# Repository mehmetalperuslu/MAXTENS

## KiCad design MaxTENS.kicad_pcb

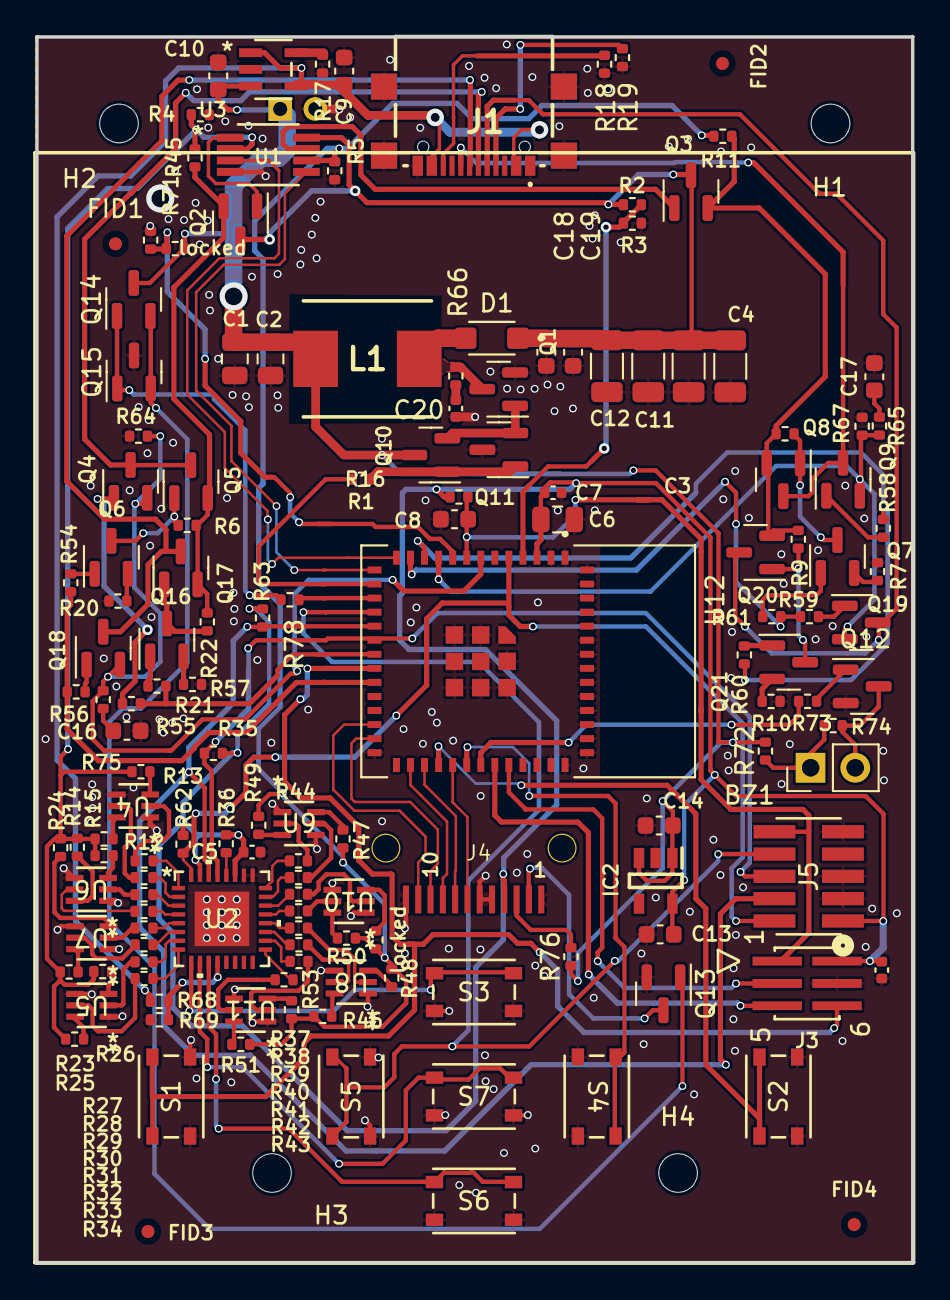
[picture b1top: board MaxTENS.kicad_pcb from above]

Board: 2 copper layers, 49.9 x 69.8 mm, 154 parts (1 on the bottom side), 128 nets.

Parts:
BZ1: Buzzer; PinHeader_1x02_P2.54mm_Vertical
C1, C2: 10uF; C_0805_2012Metric
C3, C4, C11, C12: 2.2u; C_1206_3216Metric
C5, C7, C15, C20: 0.1u; C_0402_1005Metric
C6: 22u; C_0805_2012Metric
C8, C9, C10, C13, C14, C16, C17: 1u; C_0603_1608Metric
C18: 0.1u; C_0603_1608Metric
C19: 10n; C_0603_1608Metric
D1: DSS18UTR; SODFL3618X110N
FID1, FID2, FID3, FID4: Fiducial; Fiducial_0.75mm_Mask1.5mm
H1, H2, H3, H4: MountingHole; MountingHole_2.2mm_M2
IC2: AP7366-33W5-7; SOT95P285X130-5N
J1: GSB1C41110SSHR
J3: 20021121-00006C4LF; CONN_20021121-00006C4LF_AMP
J4: Conn_01x12; FPC_TFT_LCD
J5: 20021121-00010C4LF; CONN_00010C4LF_AMP
J6: Conn_01x02_Pin; PinHeader_1x02_P2.00mm_Vertical
L1: 22uH; INDPM7366X300N
Q1: PMV37ENEAR; SOT-23
Q2, Q3, Q4, Q6, Q7, Q9, Q10, Q12, Q14, Q16, Q18, Q19, Q21: NPN; SOT-23
Q5, Q8, Q11, Q15, Q17, Q20: PNP; SOT-23
Q13: T2N7002BK,LM; SOT-23
R1, R78: 100; R_0402_1005Metric
R2: 200k; R_0402_1005Metric
R3, R13, R16, R35, R36, R49, R62, R63, R66, R68, R69: 10k; R_0402_1005Metric
R4, R5: 30k; R_0402_1005Metric
R6, R8, R9, R22, R71: 100k; R_0402_1005Metric
R7, R10, R20, R21: 1k; R_0402_1005Metric
R11, R45: 16k; R_0402_1005Metric
R12, R47: 1M; R_0402_1005Metric
R14, R50: 4.99k; R_0402_1005Metric
R15: 3.3k; R_0402_1005Metric
R17, R24, R48: 2k; R_0402_1005Metric
R18, R19: 2.2k; R_0402_1005Metric
R23, R46: 2.4k; R_0402_1005Metric
R25, R51: 1.43k; R_0402_1005Metric
R26, R53: 1.1k; R_0402_1005Metric
R27, R28, R29, R30, R31, R32, R33, R34, R37, R38, R39, R40, R41, R42, R43, R44: 510; R_0402_1005Metric
R54, R55, R56, R57, R58, R59, R60, R61: 300; R_0402_1005Metric
R64, R67: 15; R_0402_1005Metric
R65, R75: 5k; R_0402_1005Metric
R72, R73, R74: 1K; R_0402_1005Metric
R76: 10; R_0402_1005Metric
S1, S2, S3, S4, S5, S6, S7: PTS815 SJM 250 SMTR LFS; SW4_PTS815 SJM 250 SMTR LFS_CNK
U1: ADA4522-2ARMZ-R7
U2: PCAL6524HEAZ; HUQFN32_PCAL6524_NXP
U3: MCP73812T-420I/OT; SOT-23-5_MC_MCH
U4, U5, U6, U7, U8, U9, U10, U11: 2N7002KDW_R1_00001; SOT-363-6_2P2X1P35_ONS
U12: ESP32-MINI-1-N4; XCVR_ESP32-MINI-1-N4
locked: 3.3k; R_0402_1005Metric
locked#2: 33k; R_0402_1005Metric

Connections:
+3.3V: C5.2, C6.1, C7.1, C13.1, C15.2, IC2.5 (OUT), J3.1, J4.4, J5.1, R16.1, R35.1, R36.1, R62.1, R63.1, U2.27 (VDD(P)), U2.31 (VDD(I2C-BUS)), U12.3 (3V3)
+5V: C9.1, J1.A4 (VBUS_1), J1.A9 (VBUS_2), R68.2, U3.1 (CE), U3.4 (VDD)
+BATT: C1.1, C2.1, C10.1, C14.1, IC2.1 (IN), IC2.3 (EN), J6.1, L1.1, Q10.3 (C), Q14.3 (C), R72.2, R76.1, U3.3 (VBAT), locked#2.2
+OUT_1: Q2.2 (E), Q5.2 (E), Q17.2 (E), R6.2, R22.2, R45.1
+OUT_2: Q3.2 (E), Q8.2 (E), Q20.2 (E), R8.2, R9.2, R11.2
/BatteryCharger/BAT_CHG: R68.1, R69.2, U2.12 (P1_3)
/BatteryCharger/BAT_LEVEL: R71.2, U12.9 (I34), locked#2.1
/BatteryCharger/CH1_N: J1.A7 (DN1), Q17.3 (C), Q18.3 (C)
/BatteryCharger/CH1_P: J1.A6 (DP1), Q4.3 (C), Q5.3 (C)
/BatteryCharger/CH2_N: J1.B7 (DN2), Q19.3 (C), Q20.3 (C)
/BatteryCharger/CH2_P: J1.B6 (DP2), Q8.3 (C), Q9.3 (C)
/BoostConverter/VFB: R2.2, R3.1, U12.4 (I36)
/BoostConverter/VSW: R1.1, U12.15 (IO27)
/ElectrodeChannels/CH1_1: R55.2, R57.2, U12.20 (IO2)
/ElectrodeChannels/CH1_2: R54.1, R56.1, U12.22 (IO4)
/ElectrodeChannels/CH2_1: R58.2, R60.2, U12.11 (IO32)
/ElectrodeChannels/CH2_2: R59.1, R61.1, U12.12 (IO33)
/ElectrodeChannels/EL1_DET: Q4.2 (E), Q18.2 (E), R64.1, R75.2, U12.7 (I39)
/ElectrodeChannels/EL2_DET: Q9.2 (E), Q19.2 (E), R65.2, R67.1, U12.10 (I35)
/LCD/CLK: J4.9, U12.29 (IO5)
/LCD/CS: J4.8, U12.30 (IO18)
/LCD/DC: J4.7, U12.32 (IO19)
/LCD/DIN: J4.10, U12.26 (IO10)
/LCD/LCD_A: J4.3, R76.2
/LCD/LCD_BL: R78.1, U12.16 (IO14)
/LCD/LCD_K: J4.2, Q13.3 (D)
/LCD/RST: J4.11, U12.25 (IO9)
/MCU/BUZZER_MCU: R73.2, U12.34 (IO21)
/MCU/BUZZER_N: BZ1.2 (+), Q12.3 (C), R74.1
/MCU/BUZZER_P: BZ1.1 (-), R72.1, R74.2
/MCU/CH1_BTN: J3.5, S1.1, S1.2, U12.21 (IO0)
/MCU/CH2_BTN: S2.1, S2.2, U12.31 (IO23)
/MCU/EN: C8.2, J3.2, J5.10, R16.2, U12.8 (EN)
/MCU/IN1: U1.5 (INB+), U12.14 (IO26)
/MCU/IN2: U1.3 (INA+), U12.13 (IO25)
/MCU/INT_IO_EXP: J5.2, R62.2, U2.32 (*INT), U12.5 (I37)
/MCU/LEFT_BTN: S4.1, S4.2, U12.33 (IO22)
/MCU/MOSI: J5.4, R63.2, U2.30 (SDA), U12.18 (IO13)
/MCU/RIGHT_BTN: J5.8, S5.1, S5.2, U12.17 (IO12)
/MCU/RXD: J3.6, U12.35 (RXD0)
/MCU/SCK: J5.6, R35.2, U2.29 (SCL), U12.19 (IO15)
/MCU/TXD: J3.4, U12.36 (TXD0)
/Opamp/MODE_BTN: S6.1, S6.2, U2.11 (P1_2)
/Opamp/OK_BTN: S7.1, S7.2, U2.10 (P1_1)
/Opamp/OUTA: Q2.1 (B), U1.1 (OUTA)
/Opamp/OUTB: Q3.1 (B), U1.7 (OUTB)
/Opamp/P0W: R4.1, R12.1, R13.1, R14.1, R15.1, R23.1, R24.1, R25.1, R26.1, R45.2, U1.2 (INA-)
/Opamp/P1W: R5.1, R11.1, R46.1, R47.1, R48.1, R49.1, R50.1, R51.1, R53.1, U1.6 (INB-), locked.1
/Opamp/P05V: R27.1, U4.2 (G)
/Opamp/P010: R28.1, U4.5 (G)
/Opamp/P015: R29.1, U6.2 (G)
/Opamp/P15V: R37.1, U9.2 (G)
/Opamp/P020: R30.1, U6.5 (G)
/Opamp/P025: R31.1, U7.2 (G)
/Opamp/P030: R32.1, U7.5 (G)
/Opamp/P040: R33.1, U5.2 (G)
/Opamp/P050: R34.1, U5.5 (G)
/Opamp/P110: R38.1, U9.5 (G)
/Opamp/P115: R39.1, U10.2 (G)
/Opamp/P120: R40.1, U10.5 (G)
/Opamp/P125: R41.1, U8.2 (G)
/Opamp/P130: R42.1, U8.5 (G)
/Opamp/P140: R43.1, U11.2 (G)
/Opamp/P150: R44.1, U11.5 (G)
/Opamp/TIMER_BTN: S3.1, S3.2, U2.9 (P1_0)
GND: C1.2, C2.2, C3.2, C4.2, C5.1, C6.2, C7.2, C8.1, C9.2, C10.2, C11.2, C12.2, C13.2, C14.2, C15.1, C16.2, C17.2, C18.2, C19.2, C20.1, IC2.2 (GND), J1.A1 (GND_1), J1.A12 (GND_2), J1.MP1, J1.MP2, J1.MP3, J1.MP4, J3.3, J4.1, J4.5, J4.6, J4.12, J5.3, J5.5, J5.9, J6.2, Q1.2 (S), Q11.3 (C), Q12.2 (E), Q13.2 (S), Q15.3 (C), R3.2, R4.2, R5.2, R7.2, R10.2, R17.2, R18.1, R19.2, R20.2, R21.2, R64.2, R67.2, R69.1, R71.1, S1.3, S1.4, S2.3, S2.4, S3.3, S3.4, S4.3, S4.4, S5.3, S5.4, S6.3, S6.4, S7.3, S7.4, U1.4 (V-), U2.25 (VSS), U2.26 (ADDR), U2.33 (EP), U3.2 (VSS), U4.1 (S), U4.4 (S), U5.1 (S), U5.4 (S), U6.1 (S), U6.4 (S), U7.1 (S), U7.4 (S), U8.1 (S), U8.4 (S), U9.1 (S), U9.4 (S), U10.1 (S), U10.4 (S), U11.1 (S), U11.4 (S), U12.1 (GND_1), U12.2 (GND_1__1), U12.27 (GND_1__2), U12.38 (GND_1__3), U12.39 (GND_1__4), U12.40 (GND_1__5), U12.41 (GND_1__6), U12.42 (GND_1__7), U12.43 (GND_1__8), U12.44 (GND_1__9), U12.45 (GND_1__10), U12.46 (GND_1__11), U12.47 (GND_1__12), U12.48 (GND_1__13), U12.49 (GND_1__14), U12.50 (GND_2), U12.51 (GND_2__1), U12.52 (GND_2__2), U12.53 (GND_2__3), U12.54 (GND_2__4), U12.55_1 (GND_2__5), U12.55_2 (GND_2__6), U12.55_3 (GND_2__7), U12.55_4 (GND_2__8), U12.55_5 (GND_2__9), U12.55_6 (GND_2__10), U12.55_7 (GND_2__11), U12.55_8 (GND_2__12), U12.55_9 (GND_2__13)
unnamed: C16.1, R75.1
unnamed: C17.1, R65.1
unnamed: C20.2, R66.2
unnamed: J1.A5 (CC1), R19.1
unnamed: J1.B5 (CC2), R18.2
unnamed: D1.A, L1.2, Q1.3 (D), R66.1
unnamed: Q1.1 (G), Q10.2 (E), Q11.2 (E)
unnamed: Q4.1 (B), R55.1
unnamed: Q5.1 (B), Q6.3 (C), R6.1
unnamed: Q6.1 (B), R54.2
unnamed: Q6.2 (E), R20.1
unnamed: Q7.1 (B), R61.2
unnamed: Q7.3 (C), Q8.1 (B), R8.1
unnamed: Q7.2 (E), R7.1
unnamed: Q9.1 (B), R58.1
unnamed: Q10.1 (B), Q11.1 (B), R1.2
unnamed: Q12.1 (B), R73.1
unnamed: Q13.1 (G), Q14.2 (E), Q15.2 (E)
unnamed: Q14.1 (B), Q15.1 (B), R78.2
unnamed: Q16.1 (B), R57.1
unnamed: Q16.3 (C), Q17.1 (B), R22.1
unnamed: Q16.2 (E), R21.1
unnamed: Q18.1 (B), R56.2
unnamed: Q19.1 (B), R59.2
unnamed: Q20.1 (B), Q21.3 (C), R9.1
unnamed: Q21.1 (B), R60.1
unnamed: Q21.2 (E), R10.1
unnamed: R12.2, U4.6 (D)
unnamed: R13.2, U4.3 (D)
unnamed: R14.2, U6.6 (D)
unnamed: R15.2, U6.3 (D)
unnamed: R23.2, U7.6 (D)
unnamed: R24.2, U7.3 (D)
unnamed: R25.2, U5.6 (D)
unnamed: R26.2, U5.3 (D)
unnamed: R46.2, U8.6 (D)
unnamed: R47.2, U9.6 (D)
unnamed: R48.2, U8.3 (D)
unnamed: R49.2, U9.3 (D)
unnamed: R50.2, U10.6 (D)
unnamed: R51.2, U11.6 (D)
unnamed: U10.3 (D), locked.2
unnamed: R53.2, U11.3 (D)
unnamed: R36.2, U2.28 (*RESET)
unnamed: R27.2, U2.1 (P0_0)
unnamed: R28.2, U2.2 (P0_1)
unnamed: R29.2, U2.3 (P0_2)
unnamed: R30.2, U2.4 (P0_3)
unnamed: R31.2, U2.5 (P0_4)
unnamed: R32.2, U2.6 (P0_5)
unnamed: R33.2, U2.7 (P0_6)
unnamed: R34.2, U2.8 (P0_7)
unnamed: R44.2, U2.17 (P2_0)
unnamed: R43.2, U2.18 (P2_1)
unnamed: R42.2, U2.19 (P2_2)
unnamed: R41.2, U2.20 (P2_3)
unnamed: R40.2, U2.21 (P2_4)
unnamed: R39.2, U2.22 (P2_5)
unnamed: R38.2, U2.23 (P2_6)
unnamed: R37.2, U2.24 (P2_7)
unnamed: R17.1, U3.5 (PROG)
VCC: C3.1, C4.1, C11.1, C12.1, C18.1, C19.1, D1.C, Q2.3 (C), Q3.3 (C), R2.1, U1.8 (V+)

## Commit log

2023-09-30 v1.0
2023-10-20 version 2 with 0.8mm thickness
2023-11-05 v3: removed digital potentiometer, added 8 discrete resistors and one GPIO expander
2023-12-23 version 4: changed GPIO expander, added current sense resistor to electrodes, added buzzer pins, fixed some gpio inputs that needs to be pulled high, added battery charge detection, added battery lev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
2024-03-11 version 5: replaced ESP32-WROVER module with ESP-Mini, removed 2.5mm plugs, changed USB connector and routed electrode signals on it, added RC snubber circuit to boost converter and output caps to re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
2024-05-13 Fixed electrode detection mechanism, modified position of USB Type-C port
